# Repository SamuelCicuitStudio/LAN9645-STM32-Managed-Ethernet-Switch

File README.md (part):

# Ethernet Switch Project Handbook

This repository contains a managed Ethernet switch platform built around a `LAN9645` switch and an `STM32H743` management MCU. The board is designed around two active copper ports, two active SerDes paths, a CPU-facing RMII connection, SPI-based management, and a USB-first CLI and diagnostics workflow.

This `README.md` is intentionally written as the main project handbook. The goal of this file is that a user should be able to understand the hardware, the firmware structure, the boot sequence, the runtime behavior, the LAN9645 feature surface, and the current CLI without needing to open the design-side markdown files first.

## Current Status

| Area | Status | Meaning |
|---|---|---|
| Hardware architecture | Defined | The board role, major interfaces, straps, clocks, and LAN9645 pin usage are fixed. |
| LAN9645 startup straps | Defined | Managed SPI mode, RMII1 CPU link, copper LED overlap handling, and SerDes clock policy are documented and fixed. |
| STM32 control and debug pin plan | Defined | SPI, RMII, LAN reset, IRQ, USB CDC, UART4, LEDs, and user button are assigned. |
| STM32 HAL ETH + LwIP baseline | Implemented in code | The project has a generated-plus-custom Ethernet path ready for bring-up. |
| USER_PHY path | Implemented in code | The LAN9645 internal copper PHY state is exposed to Cube through the custom `USER_PHY` bridge. |
| LAN9645 low-level SPI/register/core stack | Implemented in code baseline | The firmware has a layered SPI, register, target-map, and core API. |
| LAN9645 feature modules | Implemented in code baseline | The repo contains feature-domain modules and CLI hooks for a wide control surface. |
| CLI and diagnostics framework | Implemented in code baseline | USB CDC is the default serial owner and the CLI already exposes many switch domains. |
| Real board power-on validation | Not yet performed | The board is not currently available for hardware proof. |
| Ping validation on real hardware | Not yet performed | The code path exists, but the physical test still needs to be run later. |
| Final target/register truth vs silicon | Still required | The firmware is structured for full control, but the final proof must come from real-board register readback. |

## Quick Navigation

- [1. Project Overview](#1-project-overview)
- [1.1 Project Goal](#11-project-goal)
- [1.2 Locked Project Profile](#12-locked-project-profile)
- [1.3 What Success Looks Like](#13-what-success-looks-like)
- [2. Board Images](#2-board-images)
- [3. System Architecture](#3-system-architecture)
- [3.1 High-Level View](#31-high-level-view)
- [3.2 Control Path vs Data Path](#32-control-path-vs-data-path)
- [3.3 Clocking Strategy](#33-clocking-strategy)
- [4. Hardware Platform](#4-hardware-platform)
- [4.1 LAN9645 Hardware Summary](#41-lan9645-hardware-summary)
- [4.2 Port Usage Model](#42-port-usage-model)
- [4.3 Exact Startup Strap Configuration](#43-exact-startup-strap-configuration)
- [4.4 Definitive Bootstrap Matrix](#44-definitive-bootstrap-matrix)
- [4.5 Functional Pin Assignment](#45-functional-pin-assignment)
- [4.6 Copper LED Pin Usage](#46-copper-led-pin-usage)
- [4.7 Reset and IRQ Design](#47-reset-and-irq-design)
- [4.8 Hardware Facts Software Cannot Repair](#48-hardware-facts-software-cannot-repair)
- [5. STM32H743 Interface Map](#5-stm32h743-interface-map)
- [5.1 Fixed STM32 Control and Debug Pins](#51-fixed-stm32-control-and-debug-pins)
- [5.2 STM32 Ethernet Signals](#52-stm32-ethernet-signals)
- [5.3 STM32 Board LEDs and Button](#53-stm32-board-leds-and-button)
- [5.4 STM32 Role in the System](#54-stm32-role-in-the-system)
- [5.5 RMII Reference Clock Ownership](#55-rmii-reference-clock-ownership)
- [6. Firmware Architecture](#6-firmware-architecture)
- [6.1 Locked Firmware Stack](#61-locked-firmware-stack)
- [6.2 CubeMX and LwIP Operating Model](#62-cubemx-and-lwip-operating-model)
- [6.3 Memory, DMA, Cache, and MPU Assumptions](#63-memory-dma-cache-and-mpu-assumptions)
- [6.4 Locked Static Network Plan](#64-locked-static-network-plan)
- [6.5 Responsibility Split](#65-responsibility-split)
- [6.6 LAN9645 Register Addressing Model](#66-lan9645-register-addressing-model)
- [6.7 SPI Management Transaction Format](#67-spi-management-transaction-format)
- [6.8 USER_PHY Bridge and Ethernet Glue](#68-user_phy-bridge-and-ethernet-glue)
- [6.9 Generated Code vs Project Code](#69-generated-code-vs-project-code)
- [7. Startup and Runtime Execution Model](#7-startup-and-runtime-execution-model)
- [7.1 Main Application States](#71-main-application-states)
- [7.2 Boot Sequence Overview](#72-boot-sequence-overview)
- [7.3 Detailed Startup Sequence](#73-detailed-startup-sequence)
- [7.4 Runtime Loop Responsibilities](#74-runtime-loop-responsibilities)
- [7.5 LAN IRQ Supervision Model](#75-lan-irq-supervision-model)
- [7.6 Why Some Code Stays in main.c](#76-why-some-code-stays-in-mainc)
- [8. Library Architecture](#8-library-architecture)
- [8.1 Top-Level Dependency View](#81-top-level-dependency-view)
- [8.2 Infrastructure Libraries](#82-infrastructure-libraries)
- [8.3 LAN9645 Base Control Libraries](#83-lan9645-base-control-libraries)
- [8.4 Ethernet and LwIP Glue Files](#84-ethernet-and-lwip-glue-files)
- [8.5 Feature Modules](#85-feature-modules)
- [8.6 Intended Library Usage Policy](#86-intended-library-usage-policy)
- [9. LAN9645 Control Surface](#9-lan9645-control-surface)
- [9.1 Fixed-by-Hardware vs Runtime-Controlled](#91-fixed-by-hardware-vs-runtime-controlled)
- [9.2 Bring-Up Critical Runtime Domains](#92-bring-up-critical-runtime-domains)
- [9.3 Feature Family Overview](#93-feature-family-overview)
- [9.4 Complete Feature Matrix](#94-complete-feature-matrix)
- [9.5 Default Firmware Baseline](#95-default-firmware-baseline)
- [9.6 Practical Meaning of Full Control](#96-practical-meaning-of-full-control)
- [10. CLI, Diagnostics, USB/UART, LEDs, and Button](#10-cli-diagnostics-usbuart-leds-and-button)
- [10.1 Serial Policy](#101-serial-policy)
- [10.2 CLI Usage Conventions](#102-cli-usage-conventions)
- [10.3 What `status all` Actually Shows](#103-what-status-all-actually-shows)
- [10.4 CLI Command Family Map](#104-cli-command-family-map)
- [10.5 Complete CLI Command Reference](#105-complete-cli-command-reference)
- [10.6 Diagnostics Event Catalog](#106-diagnostics-event-catalog)
- [10.7 LED Behavior](#107-led-behavior)
- [10.8 User Button Behavior](#108-user-button-behavior)
- [10.9 Serial Routing Model](#109-serial-routing-model)
- [10.10 First Commands to Type on a Fresh Boot](#1010-first-commands-to-type-on-a-fresh-boot)
- [11. Bring-Up and Ping Test Procedure](#11-bring-up-and-ping-test-procedure)
- [11.1 Preconditions Before Firmware Bring-Up](#111-preconditions-before-firmware-bring-up)
- [11.2 Mandatory Bring-Up Order](#112-mandatory-bring-up-order)
- [11.3 Locked Ping Test Network Settings](#113-locked-ping-test-network-settings)
- [11.4 Minimum CLI Checklist Before Ping](#114-minimum-cli-checklist-before-ping)
- [11.5 Expected Ping Matrix](#115-expected-ping-matrix)
- [11.6 Failure Interpretation Guide](#116-failure-interpretation-guide)
- [11.7 Validation Record Placeholder](#117-validation-record-placeholder)
- [12. Validation Status and Open Points](#12-validation-status-and-open-points)
- [12.1 What Is Already True in the Repository](#121-what-is-already-true-in-the-repository)
- [12.2 What Still Needs Real Hardware Validation](#122-what-still-needs-real-hardware-validation)
- [12.3 Important Current Risks](#123-important-current-risks)
- [12.4 Readiness Summary](#124-readiness-summary)

## 1. Project Overview

### 1.1 Project Goal

The goal of this project is to build a managed Ethernet switch board where:

- `LAN9645` performs Ethernet switching, internal PHY control, queueing, filtering, and advanced switch-domain configuration.
- `STM32H743` acts as the management CPU and the CPU-side Ethernet MAC.
- `SPI` is the management path used by the STM32 to read and write LAN9645 registers.
- `RMII1` is the CPU-facing Ethernet frame path between STM32 and LAN9645.
- `USB CDC` is the default user-facing CLI and diagnostics port.
- `UART4` is the secondary serial path for fallback debugging and capture.

The project is not trying to treat the LAN9645 as a dumb external PHY. It is trying to treat it as a managed switch that the STM32 can control at register level through a clean firmware library stack.

### 1.2 Locked Project Profile

| Item | Locked choice |
|---|---|
| Switch family | `LAN9645xS / LAN96459F` |
| Package | `128-pin TQFP` |
| Copper ports physically used | `CuPHY0`, `CuPHY1` |
| Copper target for first validation | `10/100 Mbps` only |
| SerDes paths physically used | `SerDes0`, `SerDes1` |
| SerDes reference | External low-jitter `125 MHz` oscillator |
| MCU | `STM32H743` |
| CPU Ethernet path | `RMII1` |
| Switch management path | `SPI` |
| Extra control lines | `LAN_RST`, `IRQ0` |
| Default CLI owner | `USB CDC` |
| Secondary debug path | `UART4` |
| First test objective | `ping` to STM32 through the switch |

### 1.3 What Success Looks Like

For this project, first-stage success is very concrete:

1. The LAN9645 powers up in the intended managed SPI mode.
2. The STM32 can reset it and communicate with it over SPI.
3. The fixed RMII1 CPU-facing path comes up correctly.
4. The STM32 Ethernet stack starts through HAL ETH + LwIP.
5. The board responds to `ping` at the locked static IP.
6. The user can inspect status, link state, errors, and switch-domain settings through the serial CLI.

Long-term success is broader:

1. The SPI transport is fully trusted.
2. The BSP can configure and read back the switch cleanly.
3. The firmware exposes feature-domain APIs instead of scattering raw register writes through `main.c`.
4. The CLI can act as a bring-up tool, validation tool, and long-term service tool.

## 2. Board Images

These renders are included so the user can visually identify the board orientation, connector placement, and physical layout zones.

.png>)

Use the renders to orient the board into four practical areas:

| Visual zone | What it represents |
|---|---|
| Copper side | The two copper Ethernet ports tied to `CuPHY0` and `CuPHY1` |
| SerDes side | The two SerDes/SGMII/SFP-facing paths |
| MCU/debug side | The STM32H743, USB, UART, LEDs, and user button |
| Control/power side | Reset, clock, power, decoupling, and management-support circuitry |

## 3. System Architecture

### 3.1 High-Level View

```mermaid
flowchart TD
    PC[PC / Terminal / Ping Host]
    USB[USB CDC]
    UART[UART4]
    STM32[STM32H743]
    LAN[LAN9645]
    CU0[Copper Port 0]
    CU1[Copper Port 1]
    SD0[SerDes0]
    SD1[SerDes1]
    OSC[125 MHz Oscillator]

    PC --> USB
    PC --> UART
    USB --> STM32
    UART --> STM32

    STM32 -->|SPI management| LAN
    STM32 -->|LAN_RST| LAN
    LAN -->|IRQ0| STM32
    STM32 -->|RMII1 frame path| LAN

    OSC -->|125 MHz reference| LAN

    LAN --> CU0
    LAN --> CU1
    LAN --> SD0
    LAN --> SD1
```

### 3.2 Control Path vs Data Path

This distinction is one of the most important ideas in the whole project.

| Path | Direction | Physical interface | Purpose |
|---|---|---|---|
| Management path | STM32 <-> LAN9645 | `SPI` | Read and write switch registers, configure ports, inspect status, clear events, program features |
| Interrupt path | LAN9645 -> STM32 | `IRQ0` | Notify the STM32 that the switch has a cause worth checking |
| Reset path | STM32 -> LAN9645 | `LAN_RST` | Force deterministic switch reset and strap re-latch |
| CPU frame path | STM32 <-> LAN9645 | `RMII1` | Carry actual Ethernet frames between the STM32 MAC and the switch fabric |
| Serial debug path | User <-> STM32 | `USB CDC` and `UART4` | Run CLI commands, inspect status, collect errors |

A critical consequence of this split is:

- `SPI` configures the switch.
- `RMII` carries frames.
- `IRQ0` reports events.
- The serial ports explain what is happening.

### 3.3 Clocking Strategy

The board uses two different clock domains that must not be confused.

| Clock | Owner | Destination | Purpose |
|---|---|---|---|
| `125 MHz` | External oscillator | LAN9645 `S0_CLKP` | SerDes reference clock |
| `50 MHz RMII REF_CLK` | LAN9645 | STM32 `ETH_REF_CLK` | RMII timing reference for the CPU Ethernet link |

Important design conclusions:

1. The SerDes `125 MHz` is not generated by the STM32.
2. `SD_125M` is strapped high so the LAN9645 expects the external `125 MHz` reference.
3. `SGPIO_EN` must remain low when `SD_125M=1`.
4. For this design, the LAN9645 should be treated as the generator of the RMII `REF_CLK` seen by the STM32.
5. The STM32 should not be used as the RMII clock master for this switch link.

## 4. Hardware Platform

### 4.1 LAN9645 Hardware Summary

| Domain | Selected implementation |
|---|---|
| Managed mode | Yes |
| Management host | STM32 over SPI |
| CPU-facing Ethernet | `RMII1` |
| Active copper ports | `CuPHY0`, `CuPHY1` |
| Active SerDes ports | `SerDes0`, `SerDes1` |
| JTAG | disabled by strap |
| `SD_125M` | strapped high |
| `SGPIO_EN` | strapped low |
| Copper LED pins | enabled, including strap-overlap pins |

### 4.2 Port Usage Model

The hardware physically supports more internal switch resources than the first validation path needs. This project intentionally narrows the first scope.

| Port/domain | Project role | First bring-up priority |
|---|---|---|
| `CuPHY0` | Active copper user port | High |
| `CuPHY1` | Active copper user port | High |
| CPU-facing path | STM32 conduit / CPU port via `RMII1` | High |
| `SerDes0` | Active hardware path | Medium |
| `SerDes1` | Active hardware path | Medium |
| Other internal port resources | Not the first focus | Low |

Important practical rule:

- The first code validation is built around a stable managed switch plus a working CPU port.
- The first success case is not "every switch feature is proven".
- The first success case is "the switch is controlled, the CPU port works, and ping works".

### 4.3 Exact Startup Strap Configuration

The following table is the exact startup strap plan for the selected managed SPI configuration.

| Strap | GPIO / Pin | State at reset | Typical resistor | Meaning in this project |
|---|---|---|---|---|
| `BOOT_MODE0` | `GPIO_24 / pin 70` | LOW | `10k` to GND | managed startup profile |
| `BOOT_MODE1` | `GPIO_25 / pin 68` | LOW | `10k` to GND | managed startup profile |
| `BOOT_MODE2` | `GPIO_26 / pin 67` | LOW | `10k` to GND | managed startup profile |
| `MGMT_MODE0` | `GPIO_27 / pin 66` | HIGH | `10k` to VCC | SPI client management |
| `MGMT_MODE1` | `GPIO_28 / pin 65` | HIGH | `10k` to VCC | SPI client management |
| `JTAG_ENB` | `GPIO_34 / pin 43` | HIGH | `10k` to VCC | JTAG disabled |
| `SD_125M` | `GPIO_23 / pin 71` | HIGH | `10k` to VCC | external 125 MHz SerDes reference selected |
| `SGPIO_EN` | `GPIO_22 / pin 72` | LOW | `10k` to GND | must stay low when `SD_125M=1` |
| `LOOP_EN` | `GPIO_35 / pin 42` | LOW | `10k` to GND | unmanaged loop feature forced off |
| `EEPROM_SIZE` | `GPIO_33 / pin 60` | LOW | `22k` to GND | EEPROM strap forced low, then pin reused as IRQ0 |
| `GPIO_MODE0` | `GPIO_36 / pin 41` | LOW | `10k` to GND | unmanaged GPIO mode strap forced low |
| `GPIO_MODE1` | `GPIO_37 / pin 40` | LOW | `10k` to GND | unmanaged GPIO mode strap forced low |
| `SD_MODE0` | `GPIO_39 / pin 36` | LOW | `10k` to GND | unmanaged SerDes mode strap forced low |
| `SD_MODE1` | `GPIO_40 / pin 35` | LOW | `10k` to GND | unmanaged SerDes mode strap forced low |
| `XMII_MODE0` | `GPIO_41 / pin 34` | LOW | `10k` to GND | unmanaged XMII strap forced low |
| `XMII_MODE1` | `GPIO_38 / pin 38` | LOW | `10k` to GND | unmanaged XMII strap forced low |
| `E2E_CLOCK_EN` | `GPIO_10 / pin 87` | LOW | `47k` to GND | weak strap because pin becomes RMII |
| `FLOW_EN` | `GPIO_11 / pin 86` | LOW | `47k` to GND | weak strap because pin becomes RMII |
| `EEE_EN` | `GPIO_12 / pin 85` | LOW | `47k` to GND | weak strap because pin becomes RMII |
| `LED_MODE` | `GPIO_13 / pin 83` | LOW | `47k` to GND | weak strap because pin becomes RMII |
| `CUPHY_MODE` | `GPIO_14 / pin 82` | LOW | `47k` to GND | copper unmanaged strap forced low |
| `SFP_EN` | `GPIO_15 / pin 81` | LOW | `47k` to GND | unmanaged strap forced low |

Why the weaker `47k` pull-downs on `GPIO10..15` matter:

- those pins are reused for live interface signals after reset
- weaker straps reduce dynamic loading during runtime
- they still provide deterministic strap bias during reset latch

### 4.4 Definitive Bootstrap Matrix

This is the strap-by-strap answer to the simple question: "which strap is actually used, which one is just forced, and what level must it have?"

| Strap | GPIO | TQFP pin | Used in this mode? | Required state | Project meaning |
|---|---:|---:|---|---|---|
| `BOOT_MODE0` | 24 | 70 | Mandatory | LOW | with BOOT_MODE1/2 selects managed startup |
| `BOOT_MODE1` | 25 | 68 | Mandatory | LOW | with BOOT_MODE0/2 selects managed startup |
| `BOOT_MODE2` | 26 | 67 | Mandatory | LOW | with BOOT_MODE0/1 selects managed startup |
| `MGMT_MODE0` | 27 | 66 | Mandatory | HIGH | with MGMT_MODE1 selects SPI client management |
| `MGMT_MODE1` | 28 | 65 | Mandatory | HIGH | with MGMT_MODE0 selects SPI client management |
| `JTAG_ENB` | 34 | 43 | Mandatory | HIGH | disables JTAG so the pins are not claimed by JTAG logic |
| `SD_125M` | 23 | 71 | Mandatory | HIGH | external 125 MHz SerDes reference is expected |
| `SGPIO_EN` | 22 | 72 | Constraint | LOW | must be low while `SD_125M` is high |
| `LOOP_EN` | 35 | 42 | Forced-low strap | LOW | unmanaged feature held off |
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
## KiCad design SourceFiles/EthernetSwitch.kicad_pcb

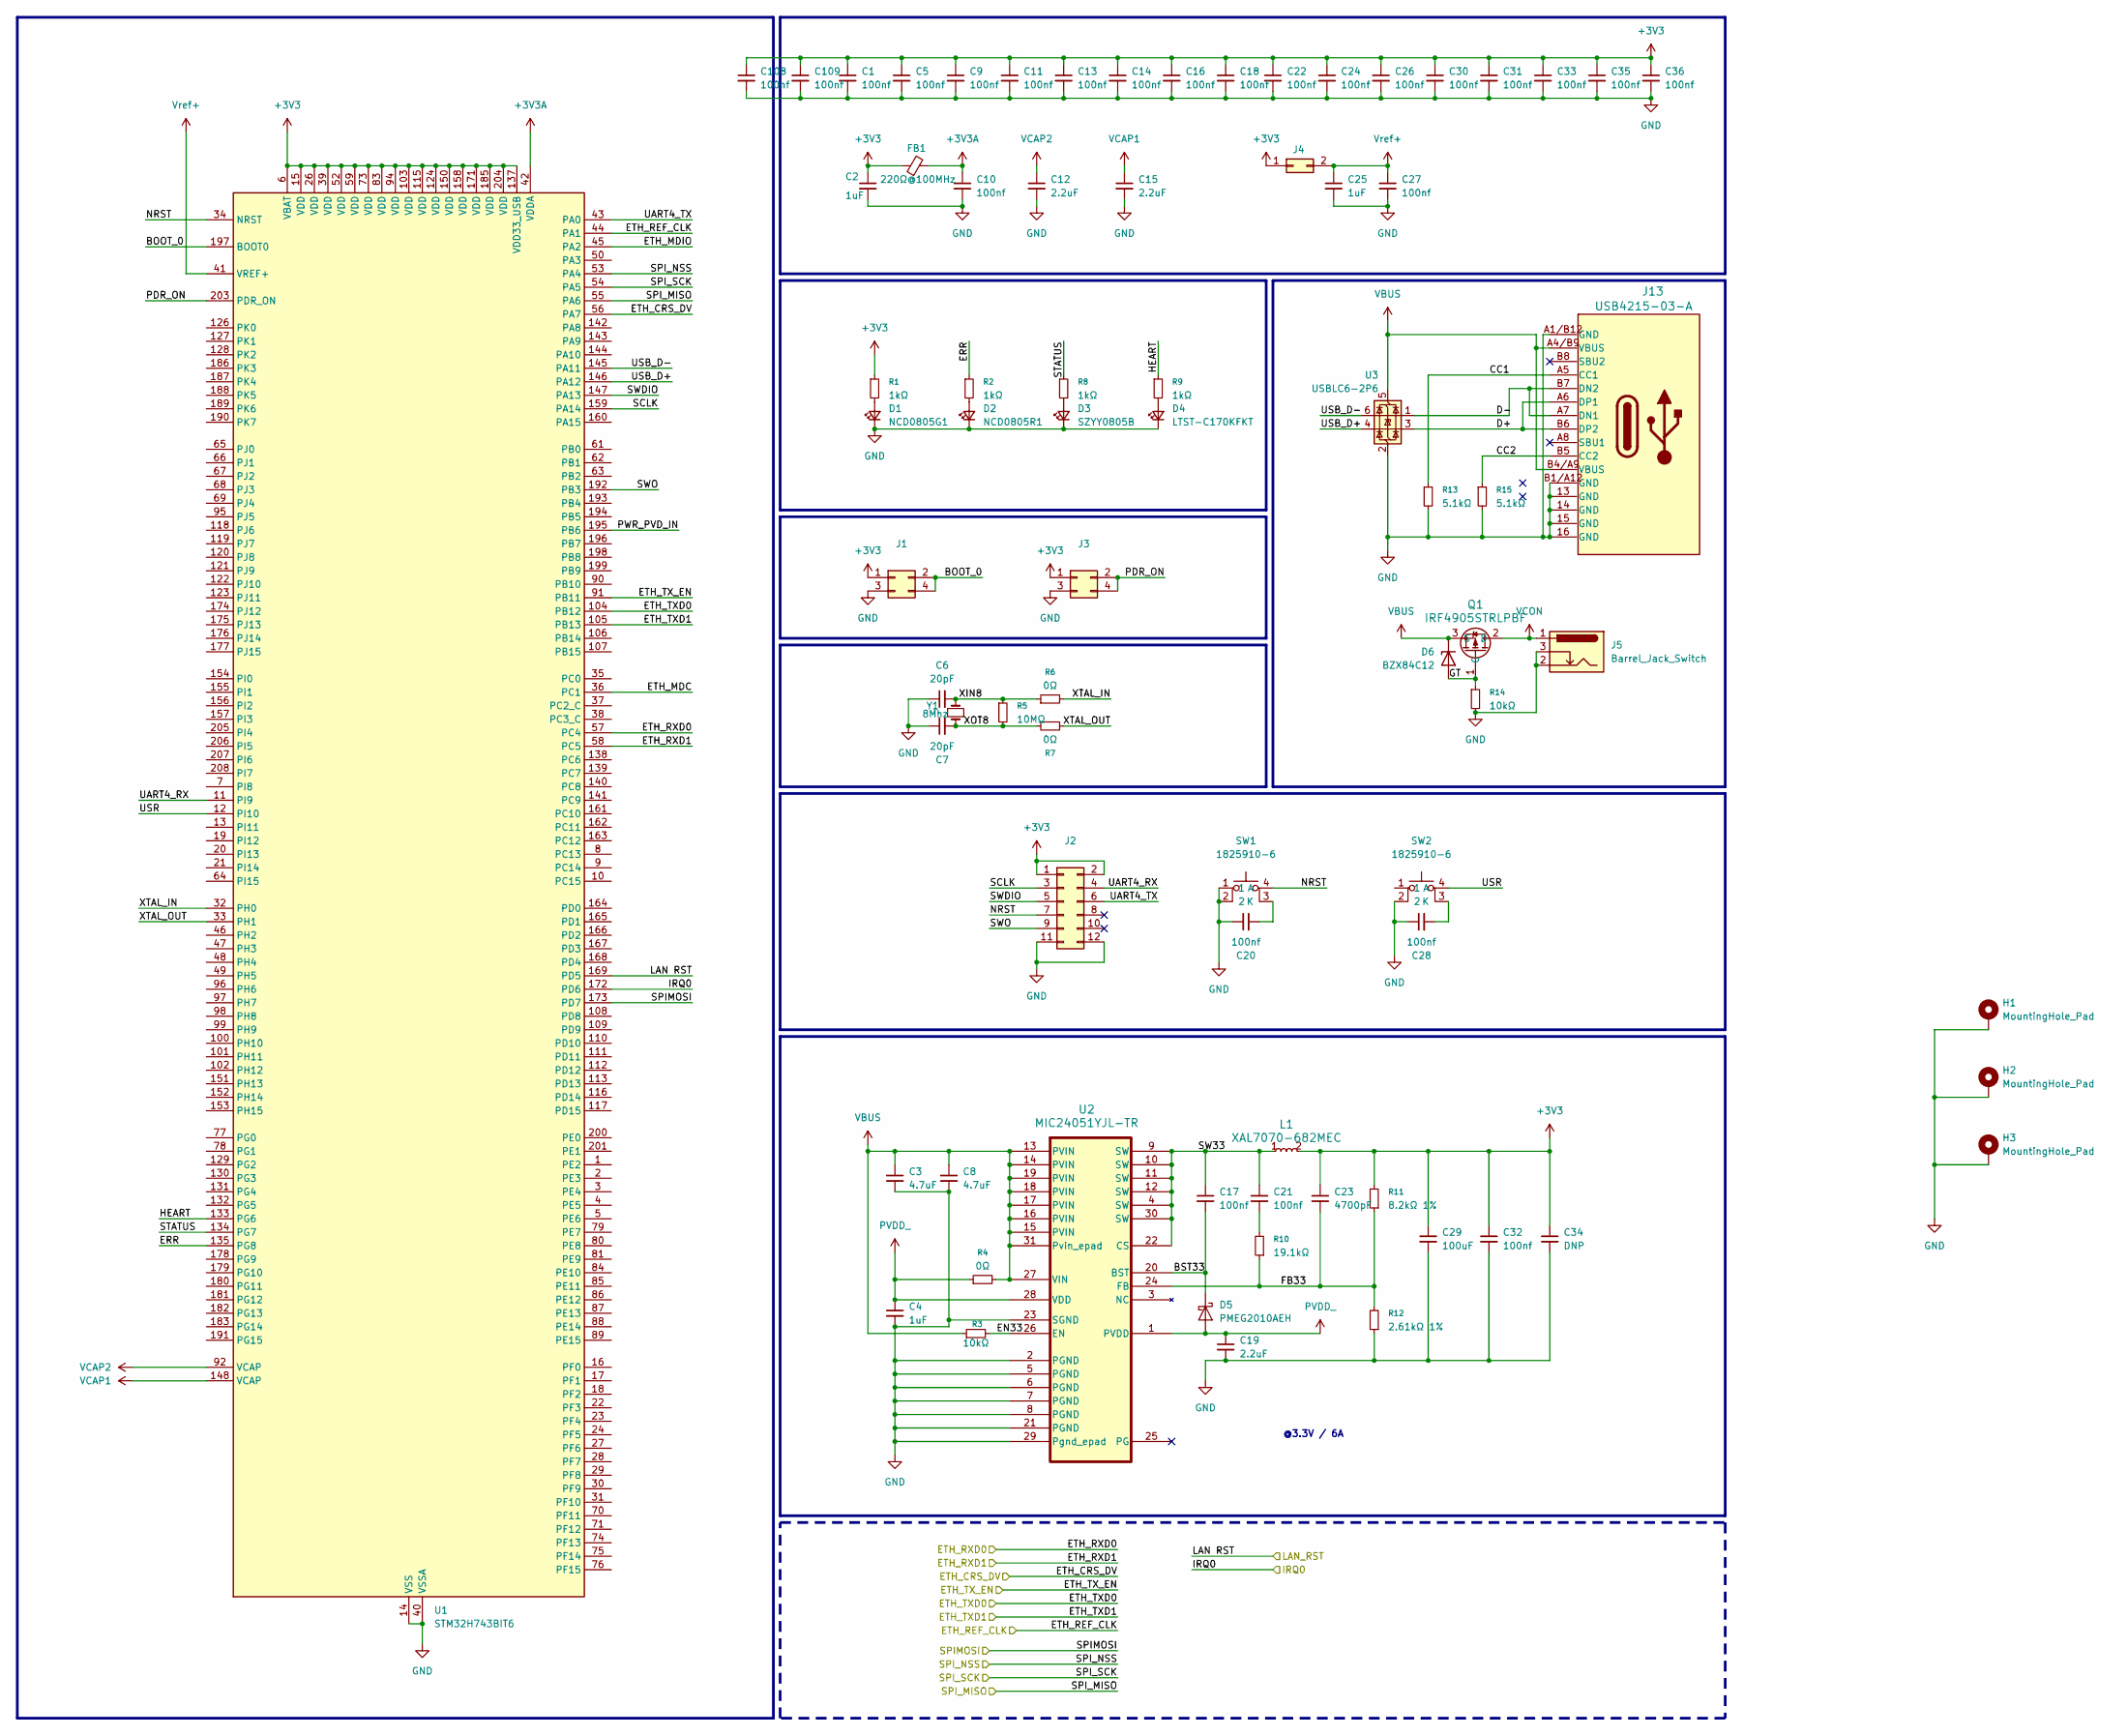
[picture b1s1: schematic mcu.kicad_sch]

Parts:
C1, C5, C9, C10, C11, C13, C14, C16, C18, C22, C24, C26, C27, C30, C31, C33, C35, C36, C108, C109: 100nf; C_0603_1608Metric
C2, C25: 1uF; C_0603_1608Metric
C3, C8: 4.7uF; C_0603_1608Metric
C4: 1uF; C_0805_2012Metric
C6, C7: 20pF; C_0805_2012Metric
C12, C15, C19: 2.2uF; C_0603_1608Metric
C17, C20, C21, C28, C32: 100nf; C_0805_2012Metric
C23: 4700pF; C_0402_1005Metric
C29: 100uF; C_1206_3216Metric
C34: DNP; C_0805_2012Metric
D1: NCD0805G1; LED_0603_1608Metric
D2: NCD0805R1; LED_0603_1608Metric
D3: SZYY0805B; LED_0603_1608Metric
D4: LTST-C170KFKT; LED_0603_1608Metric
D5: PMEG2010AEH; D_SOD-123F
D6: BZX84C12; SOT-23-3
FB1: 220Ω@100MHz; L_0805_2012Metric
H1, H2, H3: MountingHole_Pad; MountingHole_4.3mm_M4_Pad
J1, J3: Conn_02x02_Row_Letter_Last; PinHeader_2x02_P2.54mm_Vertical
J2: Conn_02x06_Row_Letter_Last; PinHeader_2x06_P2.54mm_Vertical
J4: Conn_02x01_Row_Letter_First; PinHeader_2x01_P2.54mm_Vertical
J5: Barrel_Jack_Switch; BarrelJack_GCT_DCJ200-10-A_Horizontal
J13: USB4215-03-A; CONN_8p94X6p5X3p16_12L_GCC
L1: XAL7070-682MEC; IND_XAL7070_COC
Q1: IRF4905STRLPBF; TRAN_IRF4905STRLPBF_INF
R1, R2, R8, R9: 1kΩ; R_0603_1608Metric
R3, R14: 10kΩ; R_0603_1608Metric
R4, R6, R7: 0Ω; R_0603_1608Metric
R5: 10MΩ; R_0603_1608Metric
R10: 19.1kΩ; R_0805_2012Metric
R11: 8.2kΩ 1%; R_0805_2012Metric
R12: 2.61kΩ 1%; R_0805_2012Metric
R13, R15: 5.1kΩ; R_0603_1608Metric
SW1, SW2: 1825910-6; SW_1825910-6-4; PARTREV C10
U1: STM32H743BIT6; LQFP-208_28x28mm_P0.5mm
U2: MIC24051YJL-TR; QFN28_5X6_MCH
U3: USBLC6-2P6; SOT-666
Y1: 8Mhz; Crystal_SMD_HC49-SD

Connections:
+3V3: C1.1, C2.1, C5.1, C9.1, C11.1, C13.1, C14.1, C16.1, C18.1, C22.1, C23.1, C24.1, C26.1, C29.1, C30.1, C31.1, C32.1, C33.1, C34.1, C35.1, C36.1, C108.1, C109.1, FB1.1, J1.1 (Pin_1a), J2.1 (Pin_1a), J2.2 (Pin_1b), J3.1 (Pin_1a), J4.1 (Pin_a1), L1.2, R1.1, R11.2, U1.6 (VBAT), U1.15 (VDD), U1.26 (VDD), U1.39 (VDD), U1.52 (VDD), U1.59 (VDD), U1.73 (VDD), U1.83 (VDD), U1.94 (VDD), U1.103 (VDD), U1.115 (VDD), U1.124 (VDD), U1.137 (VDD33_USB), U1.150 (VDD), U1.158 (VDD), U1.171 (VDD), U1.185 (VDD), U1.204 (VDD); also elsewhere on the board
+3V3A: C10.1, FB1.2, U1.42 (VDDA)
/MCU/BOOT_0: J1.2 (Pin_1b), J1.4 (Pin_2b), U1.197 (BOOT0)
/MCU/BST33: C17.2, D5.1 (K), U2.20 (BST)
/MCU/CC1: J13.A5 (CC1), R13.1
/MCU/CC2: J13.B5 (CC2), R15.1
/MCU/D+: J13.A6 (DP1), J13.B6 (DP2), U3.3 (I/O2)
/MCU/D-: J13.A7 (DN1), J13.B7 (DN2), U3.1 (I/O1)
/MCU/EN33: R3.2, U2.26 (EN)
/MCU/ERR: R2.1, U1.135 (PG8)
/MCU/ETH_CRS_DV: U1.56 (PA7); also elsewhere on the board
/MCU/ETH_MDC: U1.36 (PC1)
/MCU/ETH_MDIO: U1.45 (PA2)
/MCU/ETH_REF_CLK: U1.44 (PA1); also elsewhere on the board
/MCU/ETH_RXD0: U1.57 (PC4); also elsewhere on the board
/MCU/ETH_RXD1: U1.58 (PC5); also elsewhere on the board
/MCU/ETH_TXD0: U1.104 (PB12); also elsewhere on the board
/MCU/ETH_TXD1: U1.105 (PB13); also elsewhere on the board
/MCU/ETH_TX_EN: U1.91 (PB11); also elsewhere on the board
/MCU/FB33: C23.2, R10.1, R11.1, R12.2, U2.24 (FB)
/MCU/GT: D6.1 (A), Q1.1 (G), R14.1
/MCU/HEART: R9.1, U1.133 (PG6)
/MCU/IRQ0: U1.172 (PD6); also elsewhere on the board
/MCU/LAN RST: U1.169 (PD5); also elsewhere on the board
/MCU/NRST: J2.7 (Pin_4a), SW1.4 (A), U1.34 (NRST)
/MCU/PDR_ON: J3.2 (Pin_1b), J3.4 (Pin_2b), U1.203 (PDR_ON)
/MCU/PWR_PVD_IN: U1.195 (PB6)
/MCU/SCLK: J2.3 (Pin_2a), U1.159 (PA14)
/MCU/SPIMOSI: U1.173 (PD7); also elsewhere on the board
/MCU/SPI_MISO: U1.55 (PA6); also elsewhere on the board
/MCU/SPI_NSS: U1.53 (PA4); also elsewhere on the board
/MCU/SPI_SCK: U1.54 (PA5); also elsewhere on the board
/MCU/STATUS: R8.1, U1.134 (PG7)
/MCU/SW33: C17.1, C21.1, L1.1, U2.4 (SW), U2.9 (SW), U2.10 (SW), U2.11 (SW), U2.12 (SW), U2.22 (CS), U2.30 (SW)
/MCU/SWDIO: J2.5 (Pin_3a), U1.147 (PA13)
/MCU/SWO: J2.9 (Pin_5a), U1.192 (PB3)
/MCU/UART4_RX: J2.4 (Pin_2b), U1.11 (PI9)
/MCU/UART4_TX: J2.6 (Pin_3b), U1.43 (PA0)
/MCU/USB_D+: U1.146 (PA12), U3.4 (I/O2)
/MCU/USB_D-: U1.145 (PA11), U3.6 (I/O1)
/MCU/USR: SW2.4 (A), U1.12 (PI10)
/MCU/XIN8: C6.2, R5.1, R6.1, Y1.2
/MCU/XOT8: C7.2, R5.2, R7.1, Y1.1
/MCU/XTAL_IN: R6.2, U1.32 (PH0)
/MCU/XTAL_OUT: R7.2, U1.33 (PH1)
GND: C1.2, C2.2, C3.2, C4.2, C5.2, C6.1, C7.1, C8.2, C9.2, C10.2, C11.2, C12.2, C13.2, C14.2, C15.2, C16.2, C18.2, C19.2, C20.1, C22.2, C24.2, C25.2, C26.2, C27.2, C28.1, C29.2, C30.2, C31.2, C32.2, C33.2, C34.2, C35.2, C36.2, C108.2, C109.2, D1.1 (K), D2.1 (K), D3.1 (K), D4.1 (K), H1.1, H2.1, H3.1, J1.3 (Pin_2a), J2.11 (1Pin_6a), J2.12 (Pin_6b), J3.3 (Pin_2a), J5.2, J5.3, J13.13 (GND), J13.14 (GND), J13.15 (GND), J13.16 (GND), J13.A1/B12 (GND), J13.B1/A12 (GND), R12.1, R13.2, R14.2, R15.2, SW1.1, SW1.2, SW2.2, U1.14 (VSS), U1.25 (VSS), U1.40 (VSSA), U1.51 (VSS), U1.60 (VSS), U1.72 (VSS), U1.82 (VSS), U1.93 (VSS), U1.114 (VSS), U1.125 (VSS), U1.136 (VSS), U1.149 (VSS), U1.170 (VSS), U1.184 (VSS), U1.202 (VSS), U2.2 (PGND), U2.5 (PGND), U2.6 (PGND), U2.7 (PGND), U2.8 (PGND), U2.21 (PGND), U2.23 (SGND), U2.29 (Pgnd_epad), U3.2 (GND); also elsewhere on the board
unnamed: C21.2, R10.2
unnamed: D1.2 (A), R1.2
unnamed: D2.2 (A), R2.2
unnamed: D3.2 (A), R8.2
unnamed: D4.2 (A), R9.2
unnamed: C20.2, SW1.3 (K)
unnamed: C28.2, SW2.3 (K)
PVDD_: C4.1, C19.1, D5.2 (A), R4.1, U2.1 (PVDD), U2.28 (VDD)
VBUS: C3.1, C8.1, D6.3 (K), J13.A4/B9 (VBUS), J13.B4/A9 (VBUS), Q1.3 (S), R3.1, R4.2, U2.13 (PVIN), U2.14 (PVIN), U2.15 (PVIN), U2.16 (PVIN), U2.17 (PVIN), U2.18 (PVIN), U2.19 (PVIN), U2.27 (VIN), U2.31 (Pvin_epad), U3.5 (VBUS)
VCAP1: C15.1, U1.148 (VCAP)
VCAP2: C12.1, U1.92 (VCAP)
VCON: J5.1, Q1.2 (D)
Vref+: C25.1, C27.1, J4.2 (Pin_b1), U1.41 (VREF+)

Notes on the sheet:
@3.3V / 6A

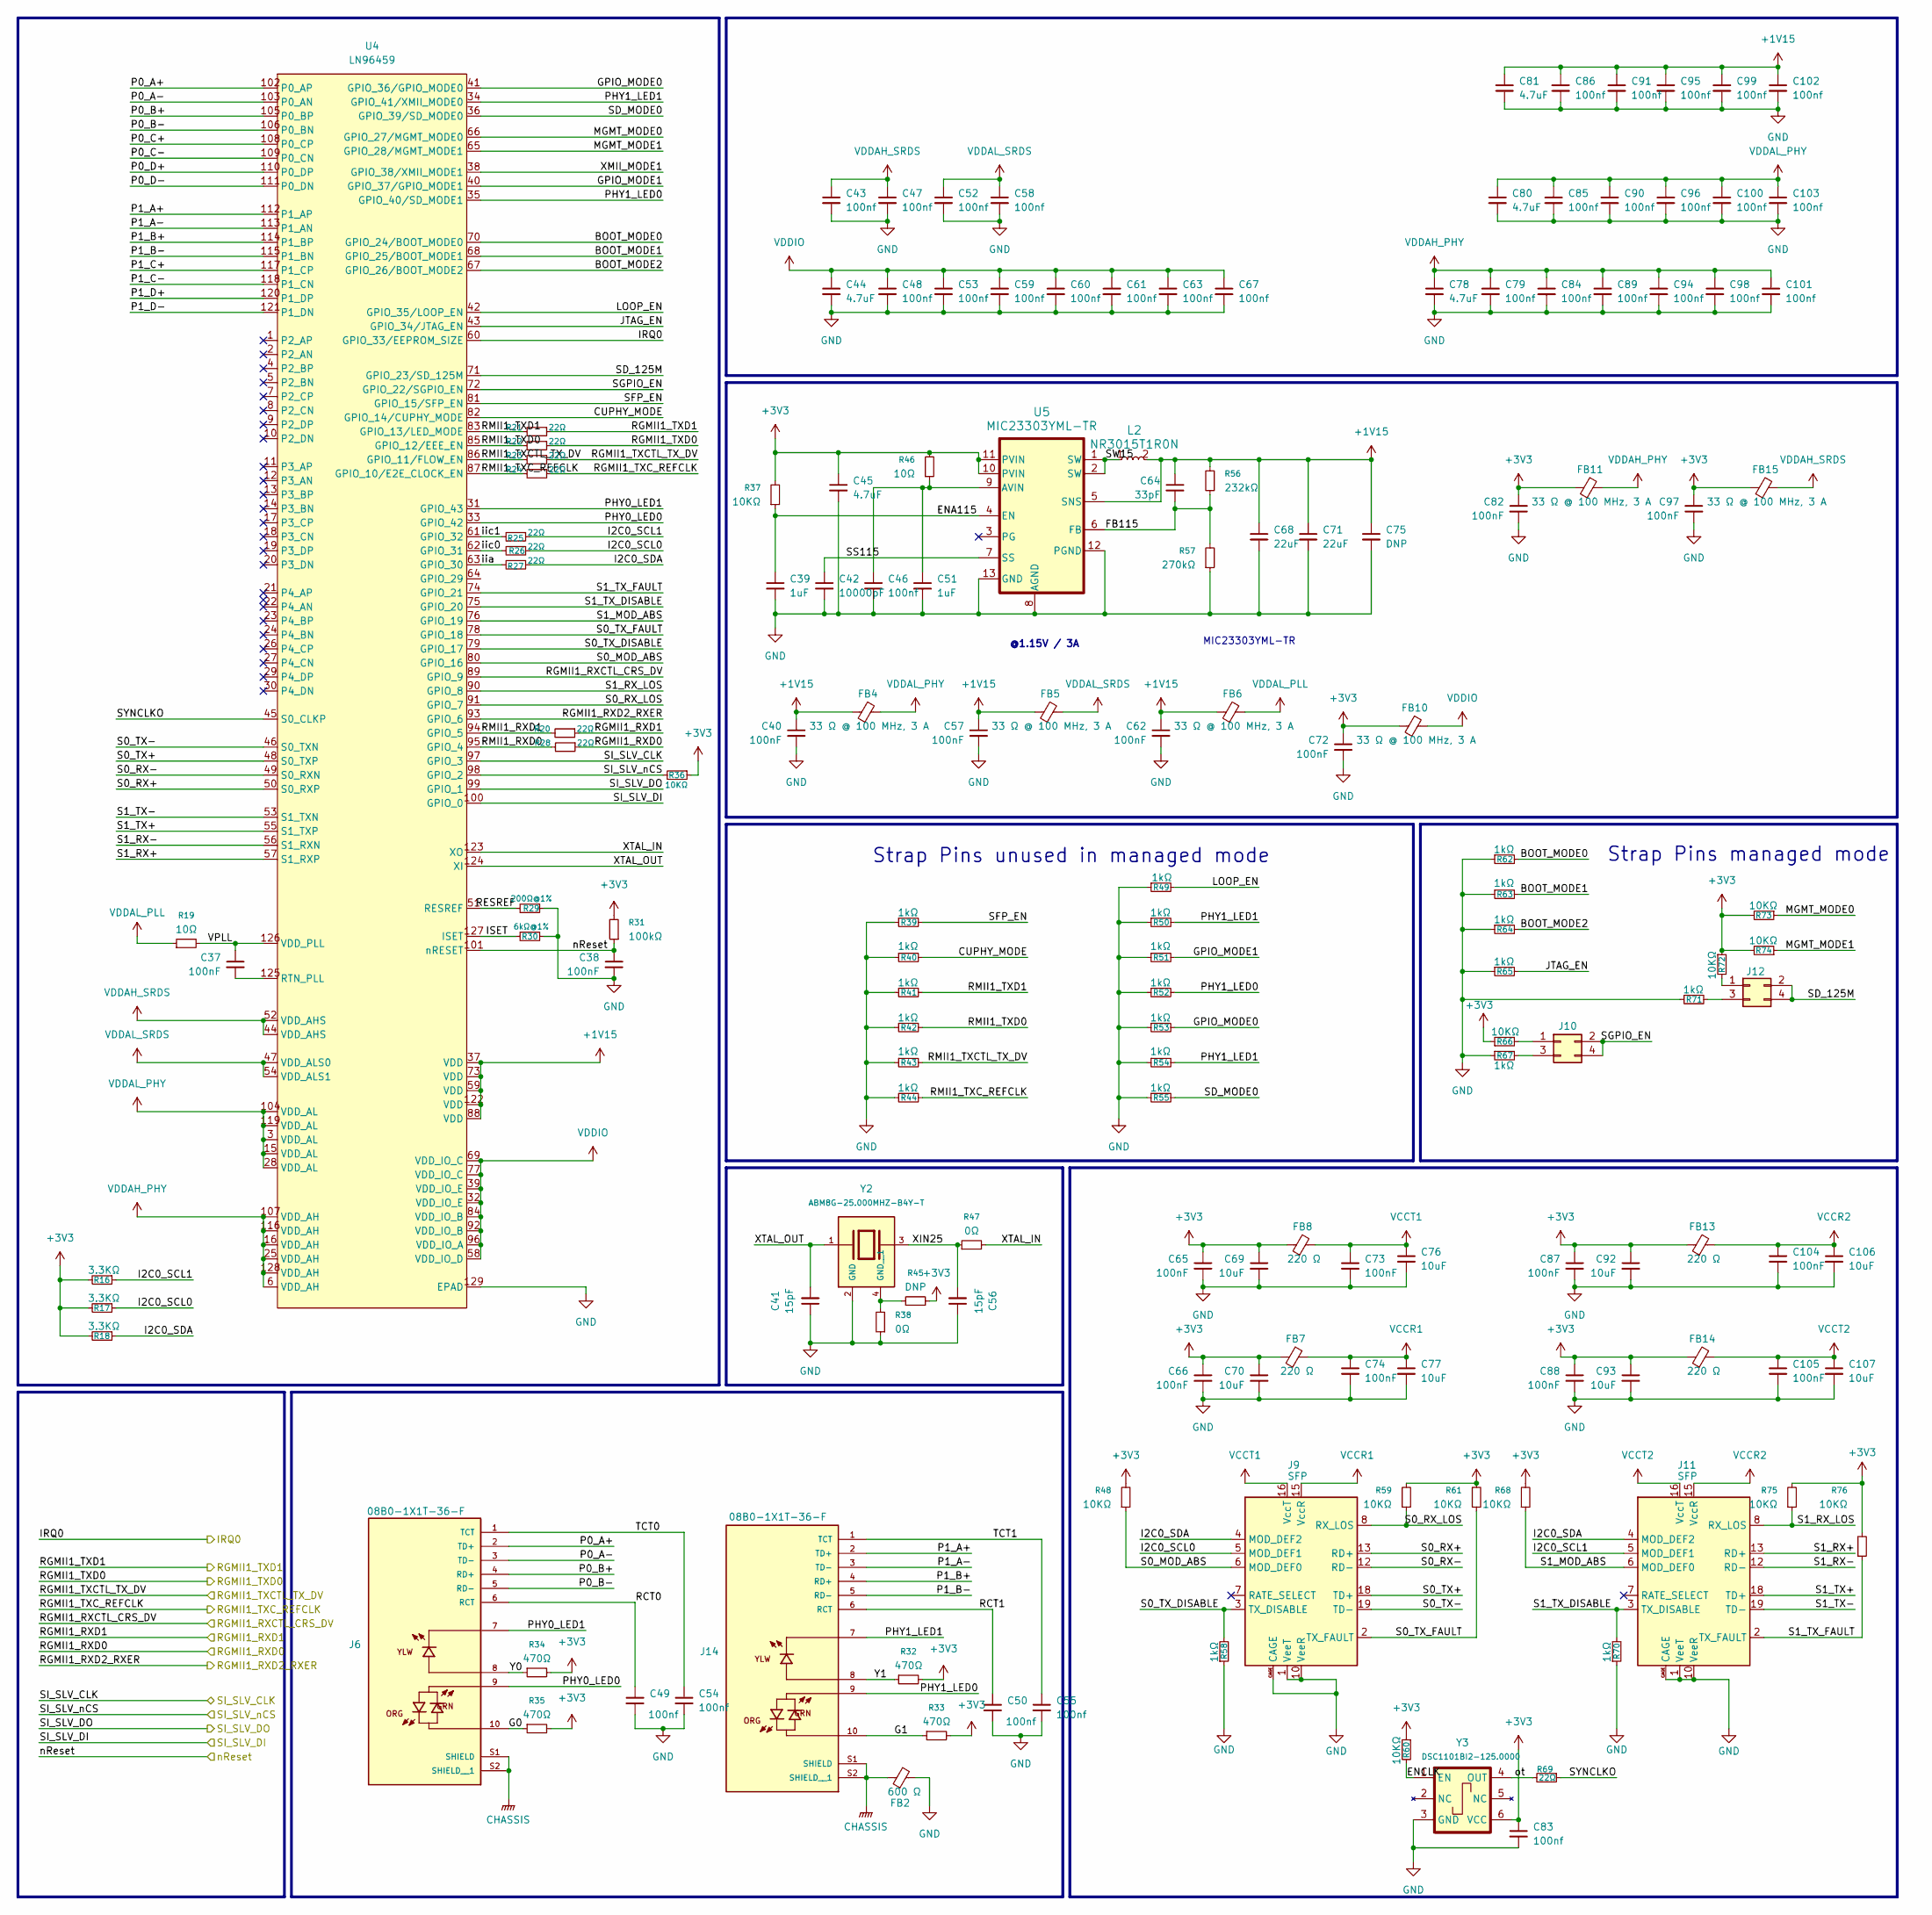
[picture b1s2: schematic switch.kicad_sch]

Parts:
C37, C38, C40, C57, C62, C65, C66, C72, C73, C74, C82, C87, C88, C97, C104, C105: 100nF; C_0603_1608Metric
C39, C51: 1uF; C_0805_2012Metric
C41, C56: 15pF; C_0603_1608Metric
C42: 10000pF; C_0402_1005Metric
C43, C48, C49, C50, C52, C53, C54, C55, C59, C60, C61, C63, C67, C79, C83, C84, C85, C86, C89, C90, C91, C94, C95, C96, C98, C99, C100, C101, C103: 100nf; C_0603_1608Metric
C44, C45, C78, C80, C81: 4.7uF; C_0603_1608Metric
C46, C47, C58, C102: 100nf; C_0805_2012Metric
C64: 33pF; C_0603_1608Metric
C68, C71: 22uF; C_0805_2012Metric
C69, C70, C76, C77, C92, C93, C106, C107: 10uF; C_0603_1608Metric
C75: DNP; C_0805_2012Metric
FB2: 600 Ω; L_0603_1608Metric
FB4, FB5, FB6, FB10, FB11, FB15: 33 Ω @ 100 MHz, 3 A; L_0603_1608Metric
FB7, FB8, FB13, FB14: 220 Ω; L_0603_1608Metric
J6, J14: 08B0-1X1T-36-F; BEL_08B0-1X1T-36-F; PARTREV D
J9, J11: SFP; Connector_SFP_and_Cage
J10, J12: Conn_02x02_Row_Letter_Last; PinHeader_2x02_P2.54mm_Vertical
L2: NR3015T1R0N; IND_TAIYO_NR3015_TAY
R16, R17, R18: 3.3KΩ; R_0603_1608Metric
R19, R46: 10Ω; R_0603_1608Metric
R20, R21, R22, R23, R24, R25, R26, R27, R28, R69: 22Ω; R_0603_1608Metric
R29: 200Ω@1%; R_0805_2012Metric
R30: 6kΩ@1%; R_0805_2012Metric
R31: 100kΩ; R_0603_1608Metric
R32, R33, R34, R35: 470Ω; R_0603_1608Metric
R36, R37, R48, R59, R60, R61, R66, R68, R72, R73, R74, R75, R76: 10KΩ; R_0603_1608Metric
R38, R47: 0Ω; R_0603_1608Metric
R39, R40, R41, R42, R43, R44, R49, R50, R51, R52, R53, R54, R55, R58, R62, R63, R64, R65, R67, R70, R71: 1kΩ; R_0603_1608Metric
R45: DNP; R_0805_2012Metric
R56: 232kΩ; R_0805_2012Metric
R57: 270kΩ; R_0603_1608Metric
U4: LN96459; 128-TQFP
U5: MIC23303YML-TR; DFN12_3X3_ML_MCH
Y2: ABM8G-25.000MHZ-B4Y-T; XTAL_ABM8G-25.000MHZ-B4Y-T; PARTREV 08.13.15
Y3: DSC1101BI2-125.0000; 6-VDFN

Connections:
+1V15: C40.1, C57.1, C62.1, C64.1, C68.1, C71.1, C75.1, C81.1, C86.1, C91.1, C95.1, C99.1, C102.1, FB4.1, FB5.1, FB6.1, L2.2, R56.2, U4.37 (VDD), U4.59 (VDD), U4.73 (VDD), U4.88 (VDD), U4.122 (VDD), U5.5 (SNS)
+3V3: C45.1, C65.1, C66.1, C69.1, C70.1, C72.1, C82.1, C83.1, C87.1, C88.1, C92.1, C93.1, C97.1, FB7.1, FB8.1, FB10.1, FB11.1, FB13.1, FB14.1, FB15.1, R16.2, R17.2, R18.2, R31.2, R32.2, R33.2, R34.2, R35.2, R36.1, R37.2, R45.2, R46.2, R48.2, R59.2, R60.1, R61.2, R66.1, R68.2, R72.1, R73.2, R74.2, R75.2, R76.2, U5.10 (PVIN), U5.11 (PVIN), Y3.6 (VCC); also elsewhere on the board
/MCU/ETH_CRS_DV: U4.89 (GPIO_9); also elsewhere on the board
/MCU/ETH_REF_CLK: R24.1; also elsewhere on the board
/MCU/ETH_RXD0: R28.1; also elsewhere on the board
/MCU/ETH_RXD1: R20.1; also elsewhere on the board
/MCU/ETH_TXD0: R22.1; also elsewhere on the board
/MCU/ETH_TXD1: R21.1; also elsewhere on the board
/MCU/ETH_TX_EN: R23.1; also elsewhere on the board
/MCU/IRQ0: U4.60 (GPIO_33/EEPROM_SIZE); also elsewhere on the board
/MCU/LAN RST: C38.1, R31.1, U4.101 (nRESET); also elsewhere on the board
/MCU/SPIMOSI: U4.100 (GPIO_0); also elsewhere on the board
/MCU/SPI_MISO: U4.99 (GPIO_1); also elsewhere on the board
/MCU/SPI_NSS: R36.2, U4.98 (GPIO_2); also elsewhere on the board
/MCU/SPI_SCK: U4.97 (GPIO_3); also elsewhere on the board
/PHY/BOOT_MODE0: R62.2, U4.70 (GPIO_24/BOOT_MODE0)
/PHY/BOOT_MODE1: R63.2, U4.68 (GPIO_25/BOOT_MODE1)
/PHY/BOOT_MODE2: R64.2, U4.67 (GPIO_26/BOOT_MODE2)
/PHY/CUPHY_MODE: R40.2, U4.82 (GPIO_14/CUPHY_MODE)
/PHY/ENA115: C39.1, R37.1, U5.4 (EN)
/PHY/ENCLK: R60.2, Y3.1 (EN)
/PHY/FB115: C64.2, R56.1, R57.2, U5.6 (FB)
/PHY/G0: J6.10, R35.1
/PHY/G1: J14.10, R33.1
/PHY/GPIO_MODE0: R53.2, U4.41 (GPIO_36/GPIO_MODE0)
/PHY/GPIO_MODE1: R51.2, U4.40 (GPIO_37/GPIO_MODE1)
/PHY/I2C0_SCL0: J9.5 (MOD_DEF1), R17.1, R26.1
/PHY/I2C0_SCL1: J11.5 (MOD_DEF1), R16.1, R25.1
/PHY/I2C0_SDA: J9.4 (MOD_DEF2), J11.4 (MOD_DEF2), R18.1, R27.1
/PHY/ISET: R30.2, U4.127 (ISET)
/PHY/JTAG_EN: R65.2, U4.43 (GPIO_34/JTAG_EN)
/PHY/LOOP_EN: R49.2, U4.42 (GPIO_35/LOOP_EN)
/PHY/MGMT_MODE0: R73.1, U4.66 (GPIO_27/MGMT_MODE0)
/PHY/MGMT_MODE1: R74.1, U4.65 (GPIO_28/MGMT_MODE1)
/PHY/P0_A+: J6.2 (TD+), U4.102 (P0_AP)
/PHY/P0_A-: J6.3 (TD-), U4.103 (P0_AN)
/PHY/P0_B+: J6.4 (RD+), U4.105 (P0_BP)
/PHY/P0_B-: J6.5 (RD-), U4.106 (P0_BN)
/PHY/P0_C+: U4.108 (P0_CP)
/PHY/P0_C-: U4.109 (P0_CN)
/PHY/P0_D+: U4.110 (P0_DP)
/PHY/P0_D-: U4.111 (P0_DN)
/PHY/P1_A+: J14.2 (TD+), U4.112 (P1_AP)
/PHY/P1_A-: J14.3 (TD-), U4.113 (P1_AN)
/PHY/P1_B+: J14.4 (RD+), U4.114 (P1_BP)
/PHY/P1_B-: J14.5 (RD-), U4.115 (P1_BN)
/PHY/P1_C+: U4.117 (P1_CP)
/PHY/P1_C-: U4.118 (P1_CN)
/PHY/P1_D+: U4.120 (P1_DP)
/PHY/P1_D-: U4.121 (P1_DN)
/PHY/PHY0_LED0: J6.9, U4.33 (GPIO_42)
/PHY/PHY0_LED1: J6.7, U4.31 (GPIO_43)
/PHY/PHY1_LED0: J14.9, R52.2, U4.35 (GPIO_40/SD_MODE1)
/PHY/PHY1_LED1: J14.7, R50.2, R54.2, U4.34 (GPIO_41/XMII_MODE0)
/PHY/RCT0: C49.1, J6.6 (RCT)
/PHY/RCT1: C50.1, J14.6 (RCT)
/PHY/RESREF: R29.2, U4.51 (RESREF)
/PHY/RGMII1_RXD2_RXER: U4.93 (GPIO_6)
/PHY/RMII1_RXD0: R28.2, U4.95 (GPIO_4)
/PHY/RMII1_RXD1: R20.2, U4.94 (GPIO_5)
/PHY/RMII1_TXCTL_TX_DV: R23.2, R43.2, U4.86 (GPIO_11/FLOW_EN)
/PHY/RMII1_TXC_REFCLK: R24.2, R44.2, U4.87 (GPIO_10/E2E_CLOCK_EN)
/PHY/RMII1_TXD0: R22.2, R42.2, U4.85 (GPIO_12/EEE_EN)
/PHY/RMII1_TXD1: R21.2, R41.2, U4.83 (GPIO_13/LED_MODE)
/PHY/S0_MOD_ABS: J9.6 (MOD_DEF0), R48.1, U4.80 (GPIO_16)
/PHY/S0_RX+: J9.13 (RD+), U4.50 (S0_RXP)
/PHY/S0_RX-: J9.12 (RD-), U4.49 (S0_RXN)
/PHY/S0_RX_LOS: J9.8 (RX_LOS), R59.1, U4.91 (GPIO_7)
/PHY/S0_TX+: J9.18 (TD+), U4.48 (S0_TXP)
/PHY/S0_TX-: J9.19 (TD-), U4.46 (S0_TXN)
/PHY/S0_TX_DISABLE: J9.3 (TX_DISABLE), R58.2, U4.79 (GPIO_17)
/PHY/S0_TX_FAULT: J9.2 (TX_FAULT), R61.1, U4.78 (GPIO_18)
/PHY/S1_MOD_ABS: J11.6 (MOD_DEF0), R68.1, U4.76 (GPIO_19)
/PHY/S1_RX+: J11.13 (RD+), U4.57 (S1_RXP)
/PHY/S1_RX-: J11.12 (RD-), U4.56 (S1_RXN)
/PHY/S1_RX_LOS: J11.8 (RX_LOS), R75.1, U4.90 (GPIO_8)
/PHY/S1_TX+: J11.18 (TD+), U4.55 (S1_TXP)
/PHY/S1_TX-: J11.19 (TD-), U4.53 (S1_TXN)
/PHY/S1_TX_DISABLE: J11.3 (TX_DISABLE), R70.2, U4.75 (GPIO_20)
/PHY/S1_TX_FAULT: J11.2 (TX_FAULT), R76.1, U4.74 (GPIO_21)
/PHY/SD_125M: J12.2 (Pin_1b), J12.4 (Pin_2b), U4.71 (GPIO_23/SD_125M)
/PHY/SD_MODE0: R55.2, U4.36 (GPIO_39/SD_MODE0)
/PHY/SFP_EN: R39.2, U4.81 (GPIO_15/SFP_EN)
/PHY/SGPIO_EN: J10.2 (Pin_1b), J10.4 (Pin_2b), U4.72 (GPIO_22/SGPIO_EN)
/PHY/SS115: C42.1, U5.7 (SS)
/PHY/SW15: L2.1, U5.1 (SW), U5.2 (SW)
/PHY/SYNCLKO: R69.1, U4.45 (S0_CLKP)
/PHY/TCT0: C54.1, J6.1 (TCT)
/PHY/TCT1: C55.1, J14.1 (TCT)
/PHY/VPLL: C37.1, R19.2, U4.126 (VDD_PLL)
/PHY/XIN25: C56.2, R47.1, Y2.3
/PHY/XMII_MODE1: U4.38 (GPIO_38/XMII_MODE1)
/PHY/XTAL_IN: R47.2, U4.123 (XO)
/PHY/XTAL_OUT: C41.2, U4.124 (XI), Y2.1
/PHY/Y0: J6.8, R34.1
/PHY/Y1: J14.8, R32.1
/PHY/iia: R27.2, U4.63 (GPIO_30)
/PHY/iic0: R26.2, U4.62 (GPIO_31)
/PHY/iic1: R25.2, U4.61 (GPIO_32)
/PHY/ot: R69.2, Y3.4 (OUT)
CHASSIS: FB2.1, J6.S1 (SHIELD), J6.S2 (SHIELD__1), J14.S1 (SHIELD), J14.S2 (SHIELD__1)
GND: C38.2, C39.2, C40.2, C41.1, C42.2, C43.2, C44.2, C45.2, C46.2, C47.2, C48.2, C49.2, C50.2, C51.2, C52.2, C53.2, C54.2, C55.2, C56.1, C57.2, C58.2, C59.2, C60.2, C61.2, C62.2, C63.2, C65.2, C66.2, C67.2, C68.2, C69.2, C70.2, C71.2, C72.2, C73.2, C74.2, C75.2, C76.2, C77.2, C78.2, C79.2, C80.2, C81.2, C82.2, C83.2, C84.2, C85.2, C86.2, C87.2, C88.2, C89.2, C90.2, C91.2, C92.2, C93.2, C94.2, C95.2, C96.2, C97.2, C98.2, C99.2, C100.2, C101.2, C102.2, C103.2, C104.2, C105.2, C106.2, C107.2, FB2.2, J9.1 (VeeT), J9.9 (VeeR), J9.10 (VeeR), J9.11 (VeeR), J9.14 (VeeR), J9.17 (VeeT), J9.20 (VeeT), J9.CAGE, J11.1 (VeeT), J11.9 (VeeR), J11.10 (VeeR), J11.11 (VeeR), J11.14 (VeeR), J11.17 (VeeT), J11.20 (VeeT), J11.CAGE, R29.1, R30.1, R38.1, R39.1, R40.1, R41.1, R42.1, R43.1, R44.1, R49.1, R50.1, R51.1, R52.1, R53.1, R54.1, R55.1, R57.1, R58.1, R62.1, R63.1, R64.1, R65.1, R67.1, R70.1, R71.1, U4.129 (EPAD), U5.8 (AGND), U5.12 (PGND), U5.13 (GND), Y2.2 (GND), Y3.3 (GND); also elsewhere on the board
unnamed: J10.1 (Pin_1a), R66.2
unnamed: J10.3 (Pin_2a), R67.2
unnamed: J12.1 (Pin_1a), R72.2
unnamed: J12.3 (Pin_2a), R71.2
unnamed: C37.2, U4.125 (RTN_PLL)
unnamed: C46.1, C51.1, R46.1, U5.9 (AVIN)
unnamed: R38.2, R45.1, Y2.4 (GND__1)
VCCR1: C74.1, C77.1, FB7.2, J9.15 (VccR)
VCCR2: C104.1, C106.1, FB13.2, J11.15 (VccR)
VCCT1: C73.1, C76.1, FB8.2, J9.16 (VccT)
VCCT2: C105.1, C107.1, FB14.2, J11.16 (VccT)
VDDAH_PHY: C78.1, C79.1, C84.1, C89.1, C94.1, C98.1, C101.1, FB11.2, U4.6 (VDD_AH), U4.16 (VDD_AH), U4.25 (VDD_AH), U4.107 (VDD_AH), U4.116 (VDD_AH), U4.128 (VDD_AH)
VDDAH_SRDS: C43.1, C47.1, FB15.2, U4.44 (VDD_AHS), U4.52 (VDD_AHS)
VDDAL_PHY: C80.1, C85.1, C90.1, C96.1, C100.1, C103.1, FB4.2, U4.3 (VDD_AL), U4.15 (VDD_AL), U4.28 (VDD_AL), U4.104 (VDD_AL), U4.119 (VDD_AL)
VDDAL_PLL: FB6.2, R19.1
VDDAL_SRDS: C52.1, C58.1, FB5.2, U4.47 (VDD_ALS0), U4.54 (VDD_ALS1)
VDDIO: C44.1, C48.1, C53.1, C59.1, C60.1, C61.1, C63.1, C67.1, FB10.2, U4.32 (VDD_IO_E), U4.39 (VDD_IO_E), U4.58 (VDD_IO_D), U4.69 (VDD_IO_C), U4.77 (VDD_IO_C), U4.84 (VDD_IO_B), U4.92 (VDD_IO_B), U4.96 (VDD_IO_A)

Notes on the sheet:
Strap Pins managed mode
MIC23303YML-TR
@1.15V / 3A
Strap Pins unused in managed mode
